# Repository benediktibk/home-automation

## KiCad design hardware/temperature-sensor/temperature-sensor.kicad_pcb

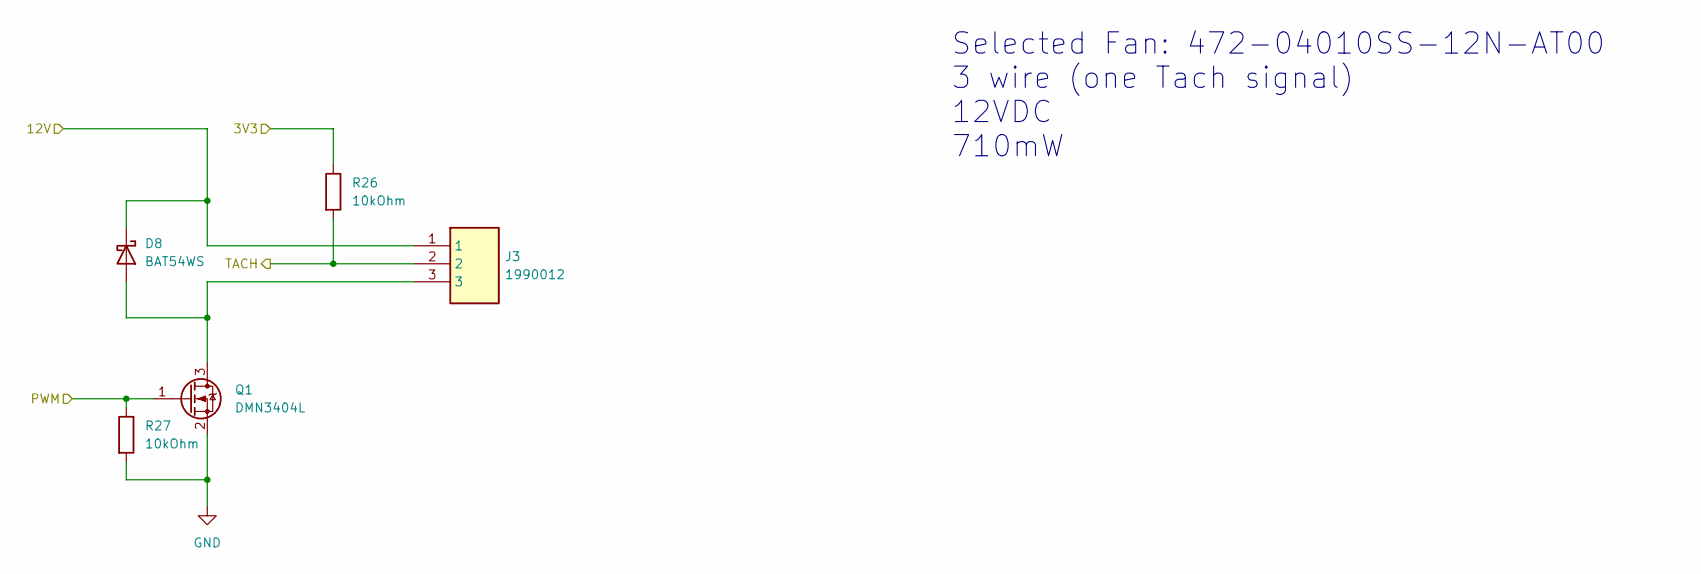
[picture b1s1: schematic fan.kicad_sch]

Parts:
D8: BAT54WS; D_SOD-323; Mouser Part Number 637-BAT54WS
J3: 1990012; Mouser Part Number 651-1990012
Q1: DMN3404L; SOT-23; Mouser Part Number 621-DMN3404L-7
R26, R27: 10kOhm; R_0603_1608Metric_Pad0.98x0.95mm_HandSolder; Mouser Part Number 652-CR0603FX-1002ELF

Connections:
/3V3: R26.1; also elsewhere on the board
/12V: D8.1 (K), J3.1; also elsewhere on the board
/Fan/PWM: Q1.1 (G), R27.1; also elsewhere on the board
/Fan/TACH: J3.2, R26.2; also elsewhere on the board
GND: Q1.2 (S), R27.2; also elsewhere on the board
unnamed: D8.2 (A), J3.3, Q1.3 (D)

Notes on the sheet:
Selected Fan: 472-04010SS-12N-AT00 3 wire (one Tach signal) 12VDC 710mW

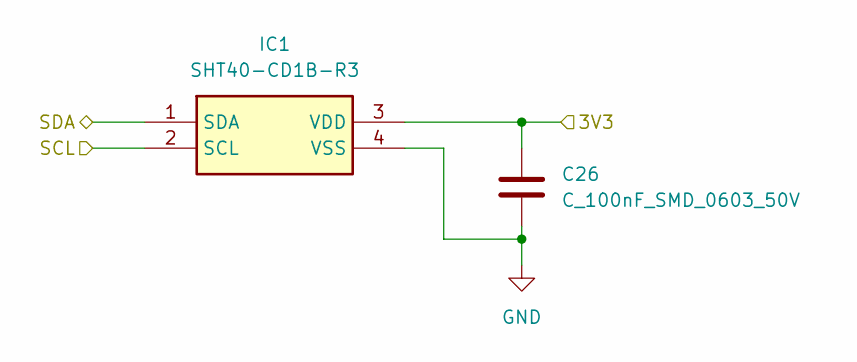
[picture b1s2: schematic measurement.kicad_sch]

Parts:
C26: C_100nF_SMD_0603_50V; C_0603_1608Metric_Pad1.08x0.95mm_HandSolder; Mouser Part Number 581-KGM15BR71H104KM
IC1: SHT40-CD1B-R3; SHT40CD1BR3; Mouser Part Number 403-SHT40-CD1B-R3

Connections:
/3V3: C26.1, IC1.3 (VDD); also elsewhere on the board
/MCU/SCL: IC1.2 (SCL); also elsewhere on the board
/MCU/SDA: IC1.1 (SDA); also elsewhere on the board
GND: C26.2, IC1.4 (VSS); also elsewhere on the board

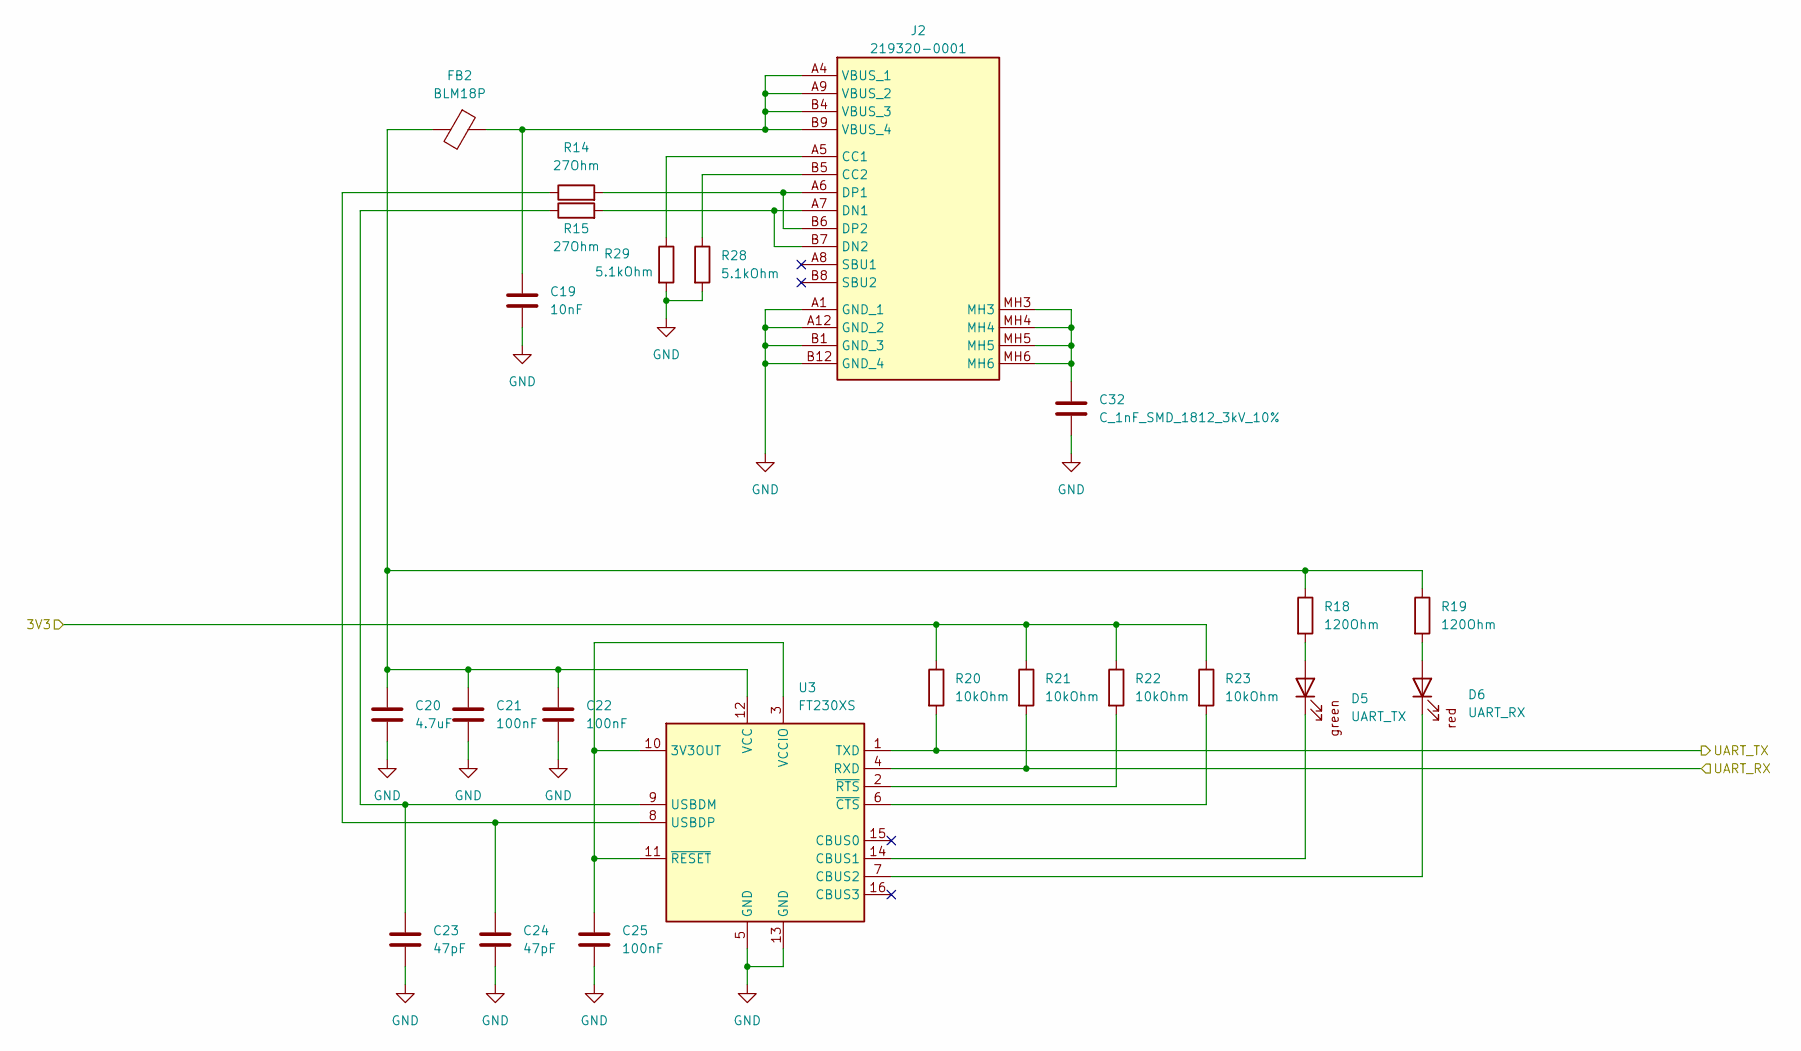
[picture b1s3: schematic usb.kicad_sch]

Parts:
C19: 10nF; C_0603_1608Metric_Pad1.08x0.95mm_HandSolder; Mouser Part Number 80-C0603C103M5R3121
C20: 4.7uF; C_0805_2012Metric_Pad1.18x1.45mm_HandSolder; Mouser Part Number 187-CL21A475KBQNNNE
C21, C22, C25: 100nF; C_0603_1608Metric_Pad1.08x0.95mm_HandSolder; Mouser Part Number 581-KGM15BR71H104KM
C23, C24: 47pF; C_0603_1608Metric_Pad1.08x0.95mm_HandSolder; Mouser Part Number 791-0603N470J101CT
C32: C_1nF_SMD_1812_3kV_10%; C_0603_1608Metric_Pad1.08x0.95mm_HandSolder; Mouser Part Number 791-1812B102K302CT
D5: UART_TX; D_0603_1608Metric_Pad1.05x0.95mm_HandSolder; Mouser Part Number 604-AP1608SGC
D6: UART_RX; D_0603_1608Metric_Pad1.05x0.95mm_HandSolder; Mouser Part Number 859-LTST-C190KDKT10A
FB2: BLM18P; R_0603_1608Metric_Pad0.98x0.95mm_HandSolder; Mouser Part Number 81-BLM11P300S
J2: 219320-0001; 2193200001; Mouser Part Number 538-219320-0001
R14, R15: 27Ohm; R_0603_1608Metric_Pad0.98x0.95mm_HandSolder; Mouser Part Number 603-RC0603FR-0727RL
R18, R19: 120Ohm; R_0603_1608Metric_Pad0.98x0.95mm_HandSolder; Mouser Part Number 603-RC0603FR-07120RL
R20, R21, R22, R23: 10kOhm; R_0603_1608Metric_Pad0.98x0.95mm_HandSolder; Mouser Part Number 652-CR0603FX-1002ELF
R28, R29: 5.1kOhm; R_0603_1608Metric_Pad0.98x0.95mm_HandSolder; Mouser Part Number 303-0603SAF5101T5E
U3: FT230XS; SSOP-16_3.9x4.9mm_P0.635mm; Mouser Part Number 895-FT230XS-R

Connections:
/3V3: R20.1, R21.1, R22.1, R23.1; also elsewhere on the board
/MCU/UART_RX: R20.2, U3.1 (TXD); also elsewhere on the board
/MCU/UART_TX: R21.2, U3.4 (RXD); also elsewhere on the board
GND: C19.2, C20.2, C21.2, C22.2, C23.2, C24.2, C25.2, C32.2, J2.A1 (GND_1), J2.A12 (GND_2), J2.B1 (GND_3), J2.B12 (GND_4), R28.2, R29.2, U3.5 (GND), U3.13 (GND); also elsewhere on the board
unnamed: C32.1, J2.MH3, J2.MH4, J2.MH5, J2.MH6
unnamed: D5.2 (A), R18.2
unnamed: D5.1 (K), U3.14 (CBUS1)
unnamed: D6.2 (A), R19.2
unnamed: D6.1 (K), U3.7 (CBUS2)
unnamed: J2.A5 (CC1), R29.1
unnamed: J2.B5 (CC2), R28.1
unnamed: J2.A7 (DN1), J2.B7 (DN2), R15.2
unnamed: J2.A6 (DP1), J2.B6 (DP2), R14.2
unnamed: C19.1, FB2.1, J2.A4 (VBUS_1), J2.A9 (VBUS_2), J2.B4 (VBUS_3), J2.B9 (VBUS_4)
unnamed: C25.1, U3.3 (VCCIO), U3.10 (3V3OUT), U3.11 (~RESET)
unnamed: C23.1, R15.1, U3.9 (USBDM)
unnamed: C24.1, R14.1, U3.8 (USBDP)
unnamed: C20.1, C21.1, C22.1, FB2.2, R18.1, R19.1, U3.12 (VCC)
unnamed: R23.2, U3.6 (~CTS)
unnamed: R22.2, U3.2 (~RTS)

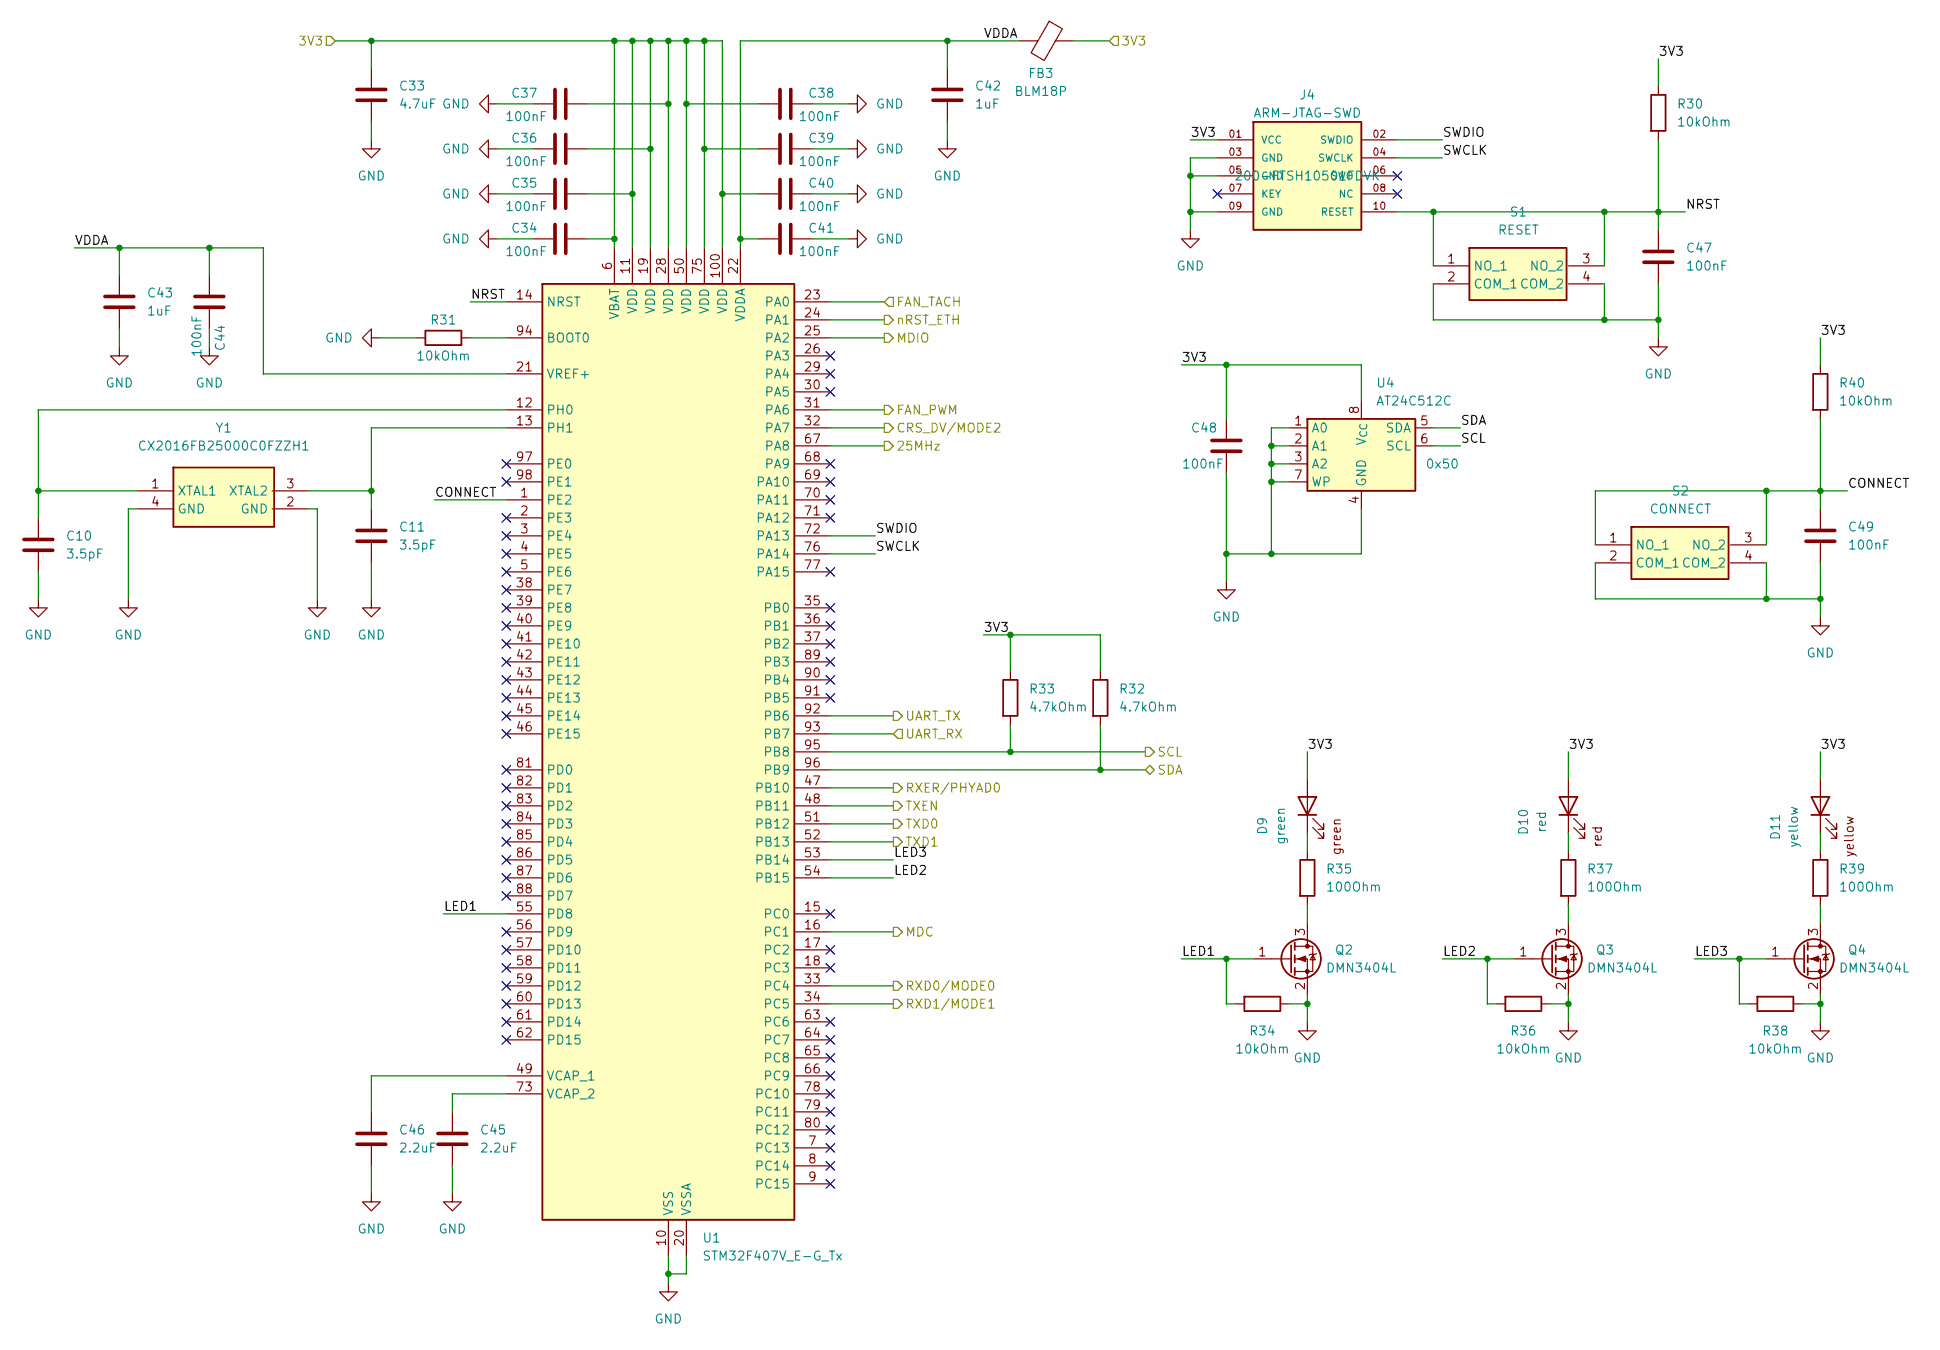
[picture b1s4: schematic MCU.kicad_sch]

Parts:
C10, C11: 3.5pF; C_0603_1608Metric_Pad1.08x0.95mm_HandSolder; Mouser Part Number 80-CBR06C359B5GAC
C33: 4.7uF; C_0805_2012Metric_Pad1.18x1.45mm_HandSolder; Mouser Part Number 187-CL21A475KBQNNNE
C34, C35, C36, C37, C38, C39, C40, C41, C44, C47, C48, C49: 100nF; C_0603_1608Metric_Pad1.08x0.95mm_HandSolder; Mouser Part Number 581-KGM15BR71H104KM
C42, C43: 1uF; C_0603_1608Metric_Pad1.08x0.95mm_HandSolder; Mouser Part Number 963-UMK107BJ105KA-T
C45, C46: 2.2uF; C_0603_1608Metric_Pad1.08x0.95mm_HandSolder; Mouser Part Number 187-CL10A225KP8NNND
D9: green; D_0603_1608Metric_Pad1.05x0.95mm_HandSolder; Mouser Part Number 604-AP1608SGC
D10: red; D_0603_1608Metric_Pad1.05x0.95mm_HandSolder; Mouser Part Number 859-LTST-C190KDKT10A
D11: yellow; D_0603_1608Metric_Pad1.05x0.95mm_HandSolder; Mouser Part Number 604-APG1608SYKC/T
FB3: BLM18P; R_0603_1608Metric_Pad0.98x0.95mm_HandSolder; Mouser Part Number 81-BLM11P300S
J4: ARM-JTAG-SWD; SAMTEC_FTSH-105-01-F-DV-P-TR; Mouser Part Number 200-FTSH10501FDVK
Q2, Q3, Q4: DMN3404L; SOT-23; Mouser Part Number 621-DMN3404L-7
R30, R31, R34, R36, R38, R40: 10kOhm; R_0603_1608Metric_Pad0.98x0.95mm_HandSolder; Mouser Part Number 652-CR0603FX-1002ELF
R32, R33: 4.7kOhm; R_0603_1608Metric_Pad0.98x0.95mm_HandSolder; Mouser Part Number 652-CR0603FX-4701ELF
R35, R37, R39: 100Ohm; R_0603_1608Metric_Pad0.98x0.95mm_HandSolder; Mouser Part Number 279-CRGH0603F100R
S1: RESET; TS046673BK100SMT; Mouser Part Number 179-TS046673BK100SMT
S2: CONNECT; TS046673BK100SMT; Mouser Part Number 179-TS046673BK100SMT
U1: STM32F407V_E-G_Tx; LQFP-100_14x14mm_P0.5mm; Mouser Part Number 511-STM32F407VGT6
U4: AT24C512C; SOIC127P600X175-8N; Mouser Part Number 556-AT24C512C-SSHM-T
Y1: CX2016FB25000C0FZZH1; Mouser Part Number 581-CX2016FB25C0FZZH

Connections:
/3V3: C33.1, C34.1, C35.1, C36.1, C37.1, C38.1, C39.1, C40.1, C48.1, D9.2 (A), D10.2 (A), D11.2 (A), FB3.1, J4.01 (VCC), R30.1, R32.1, R33.1, R40.1, U1.6 (VBAT), U1.11 (VDD), U1.19 (VDD), U1.28 (VDD), U1.50 (VDD), U1.75 (VDD), U1.100 (VDD), U4.8 (V_{CC}); also elsewhere on the board
/Ethernet/25MHz: U1.67 (PA8); also elsewhere on the board
/Ethernet/CRS_DV/MODE2: U1.32 (PA7); also elsewhere on the board
/Ethernet/MDC: U1.16 (PC1); also elsewhere on the board
/Ethernet/MDIO: U1.25 (PA2); also elsewhere on the board
/Ethernet/RXD0/MODE0: U1.33 (PC4); also elsewhere on the board
/Ethernet/RXD1/MODE1: U1.34 (PC5); also elsewhere on the board
/Ethernet/RXER/PHYAD0: U1.47 (PB10); also elsewhere on the board
/Ethernet/TXD0: U1.51 (PB12); also elsewhere on the board
/Ethernet/TXD1: U1.52 (PB13); also elsewhere on the board
/Ethernet/TXEN: U1.48 (PB11); also elsewhere on the board
/Ethernet/nRST: U1.24 (PA1); also elsewhere on the board
/Fan/PWM: U1.31 (PA6); also elsewhere on the board
/Fan/TACH: U1.23 (PA0); also elsewhere on the board
/MCU/CONNECT: C49.1, R40.2, S2.1 (NO_1), S2.3 (NO_2), U1.1 (PE2)
/MCU/LED1: Q2.1 (G), R34.2, U1.55 (PD8)
/MCU/LED2: Q3.1 (G), R36.2, U1.54 (PB15)
/MCU/LED3: Q4.1 (G), R38.2, U1.53 (PB14)
/MCU/NRST: C47.1, J4.10 (RESET), R30.2, S1.1 (NO_1), S1.3 (NO_2), U1.14 (NRST)
/MCU/SCL: R33.2, U1.95 (PB8), U4.6 (SCL); also elsewhere on the board
/MCU/SDA: R32.2, U1.96 (PB9), U4.5 (SDA); also elsewhere on the board
/MCU/SWCLK: J4.04 (SWCLK), U1.76 (PA14)
/MCU/SWDIO: J4.02 (SWDIO), U1.72 (PA13)
/MCU/UART_RX: U1.93 (PB7); also elsewhere on the board
/MCU/UART_TX: U1.92 (PB6); also elsewhere on the board
/MCU/VDDA: C41.1, C42.1, C43.1, C44.1, FB3.2, U1.21 (VREF+), U1.22 (VDDA)
GND: C10.2, C11.2, C33.2, C34.2, C35.2, C36.2, C37.2, C38.2, C39.2, C40.2, C41.2, C42.2, C43.2, C44.2, C45.2, C46.2, C47.2, C48.2, C49.2, J4.03 (GND), J4.05 (GND), J4.09 (GND), Q2.2 (S), Q3.2 (S), Q4.2 (S), R31.1, R34.1, R36.1, R38.1, S1.2 (COM_1), S1.4 (COM_2), S2.2 (COM_1), S2.4 (COM_2), U1.10 (VSS), U1.20 (VSSA), U1.27 (VSS), U1.74 (VSS), U1.99 (VSS), U4.1 (A0), U4.2 (A1), U4.3 (A2), U4.4 (GND), U4.7 (WP), Y1.2 (GND), Y1.4 (GND); also elsewhere on the board
unnamed: D9.1 (K), R35.1
unnamed: D10.1 (K), R37.1
unnamed: D11.1 (K), R39.1
unnamed: Q2.3 (D), R35.2
unnamed: Q3.3 (D), R37.2
unnamed: Q4.3 (D), R39.2
unnamed: R31.2, U1.94 (BOOT0)
unnamed: C10.1, U1.12 (PH0), Y1.1 (XTAL1)
unnamed: C11.1, U1.13 (PH1), Y1.3 (XTAL2)
unnamed: C46.1, U1.49 (VCAP_1)
unnamed: C45.1, U1.73 (VCAP_2)

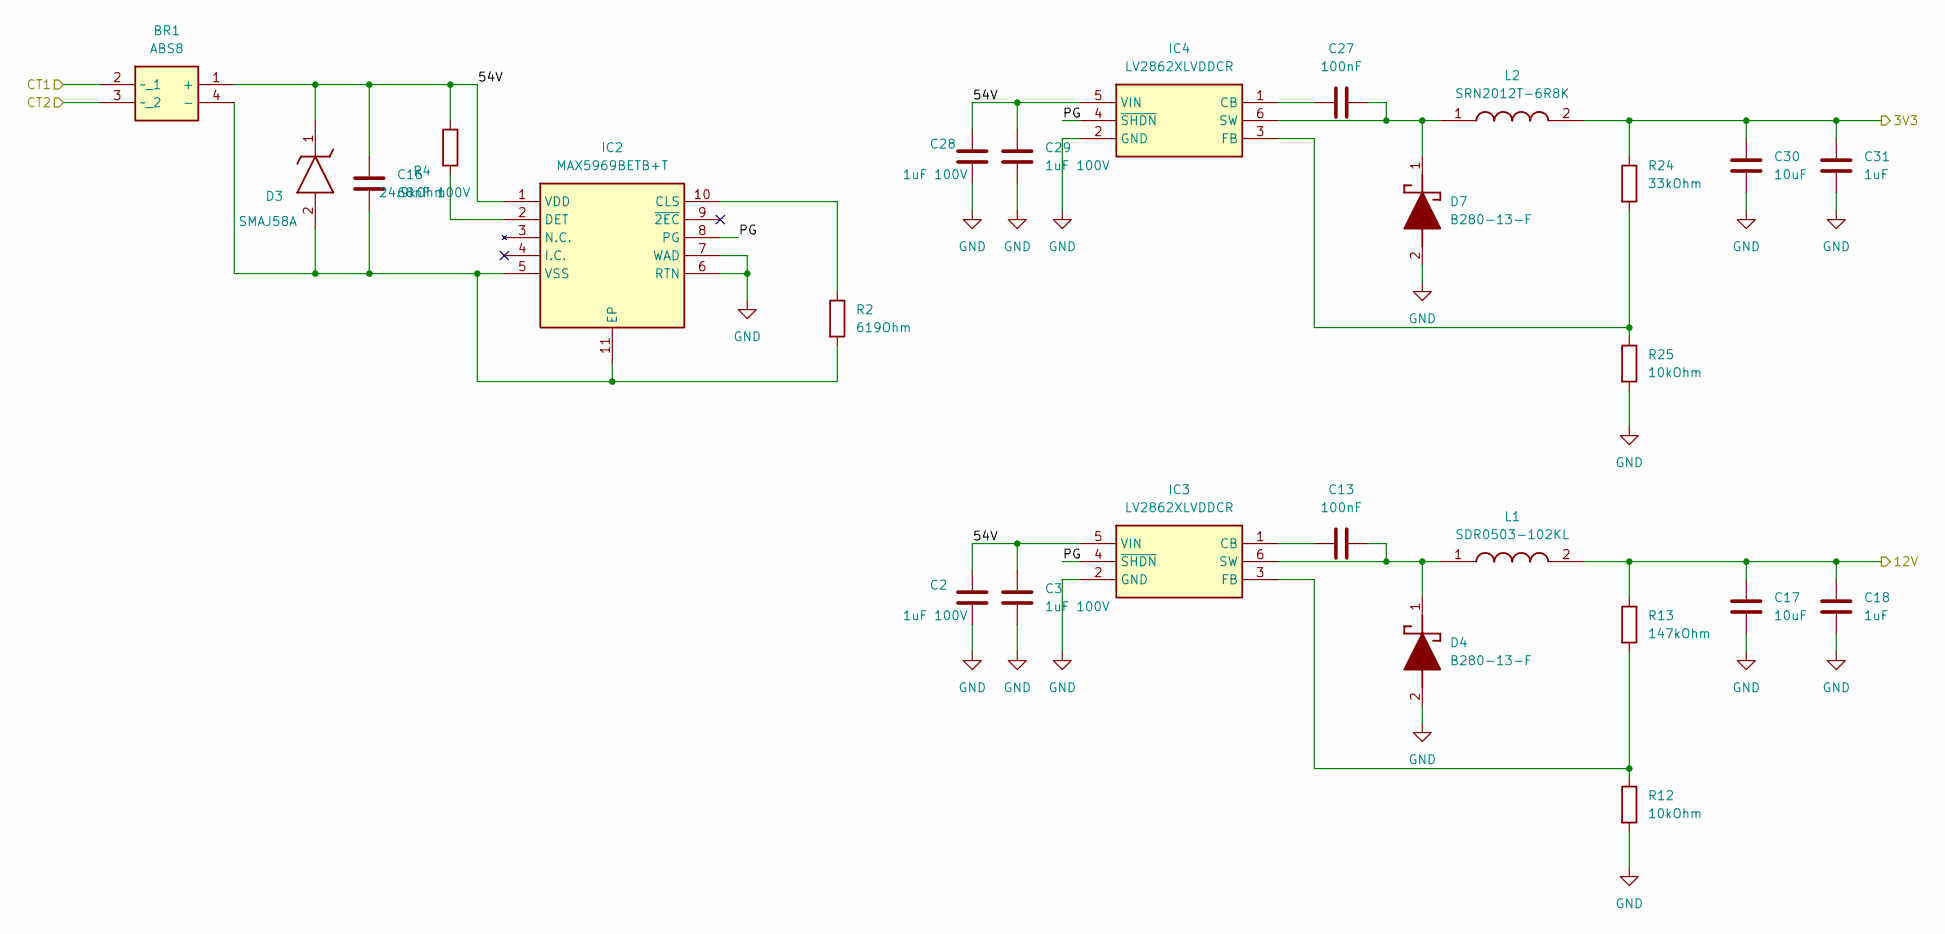
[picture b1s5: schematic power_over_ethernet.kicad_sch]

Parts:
BR1: ABS8; Mouser Part Number 637-ABS8
C2, C3, C28, C29: 1uF 100V; C_0603_1608Metric_Pad1.08x0.95mm_HandSolder; Mouser Part Number 810-C1608X7R2A105K08
C13, C27: 100nF; C_0603_1608Metric_Pad1.08x0.95mm_HandSolder; Mouser Part Number 581-KGM15BR71H104KM
C16: 68nF 100V; C_0603_1608Metric_Pad1.08x0.95mm_HandSolder; Mouser Part Number 791-0603B683K101CT
C17, C30: 10uF; C_1210_3225Metric_Pad1.33x2.70mm_HandSolder; Mouser Part Number 187-CL31A106MBHNNNE
C18, C31: 1uF; C_0603_1608Metric_Pad1.08x0.95mm_HandSolder; Mouser Part Number 963-UMK107BJ105KA-T
D3: SMAJ58A; DIOM5026X229N; Mouser Part Number 576-SMAJ58A
D4, D7: B280-13-F; DIOM5336X250N; Mouser Part Number 621-B280-13-F
IC2: MAX5969BETB+T; SON50P300X300X80-11N; Mouser Part Number 700-MAX5969BETB+T
IC3, IC4: LV2862XLVDDCR; SOT95P280X110-6N; Mouser Part Number 595-LV2862XLVDDCR
L1: SDR0503-102KL; SDR0503102KL; Mouser Part Number 652-SDR0503-102KL
L2: SRN2012T-6R8K; INDPM2012X120N; Mouser Part Number 652-SRN2012T-6R8K
R2: 619Ohm; R_0603_1608Metric_Pad0.98x0.95mm_HandSolder; Mouser Part Number 603-RT0603FRE07619RL
R4: 24.9kOhm; R_0603_1608Metric_Pad0.98x0.95mm_HandSolder; Mouser Part Number 594-MCT06030C2492FP5
R12, R25: 10kOhm; R_0603_1608Metric_Pad0.98x0.95mm_HandSolder; Mouser Part Number 652-CR0603FX-1002ELF
R13: 147kOhm; R_0603_1608Metric_Pad0.98x0.95mm_HandSolder; Mouser Part Number 594-MCT06030C1473FP5
R24: 33kOhm; R_0603_1608Metric_Pad0.98x0.95mm_HandSolder; Mouser Part Number 594-MCT06030C3302FP5

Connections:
/3V3: C30.1, C31.1, L2.2, R24.1; also elsewhere on the board
/12V: C17.1, C18.1, L1.2, R13.1; also elsewhere on the board
/Ethernet/CT1: BR1.2 (~_1); also elsewhere on the board
/Ethernet/CT2: BR1.3 (~_2); also elsewhere on the board
/Power over Ethernet/54V: BR1.1 (+), C2.1, C3.1, C16.1, C28.1, C29.1, D3.1 (K), IC2.1 (VDD), IC3.5 (VIN), IC4.5 (VIN), R4.1
/Power over Ethernet/PG: IC2.8 (PG), IC3.4 (~SHDN), IC4.4 (~SHDN)
GND: C2.2, C3.2, C17.2, C18.2, C28.2, C29.2, C30.2, C31.2, D4.2 (A), D7.2 (A), IC2.6 (RTN), IC2.7 (WAD), IC3.2 (GND), IC4.2 (GND), R12.2, R25.2; also elsewhere on the board
unnamed: BR1.4 (-), C16.2, D3.2 (A), IC2.5 (VSS), IC2.11 (EP), R2.2
unnamed: C13.1, D4.1 (K), IC3.6 (SW), L1.1
unnamed: C27.1, D7.1 (K), IC4.6 (SW), L2.1
unnamed: IC2.10 (CLS), R2.1
unnamed: IC2.2 (DET), R4.2
unnamed: C13.2, IC3.1 (CB)
unnamed: IC3.3 (FB), R12.1, R13.2
unnamed: C27.2, IC4.1 (CB)
unnamed: IC4.3 (FB), R24.2, R25.1

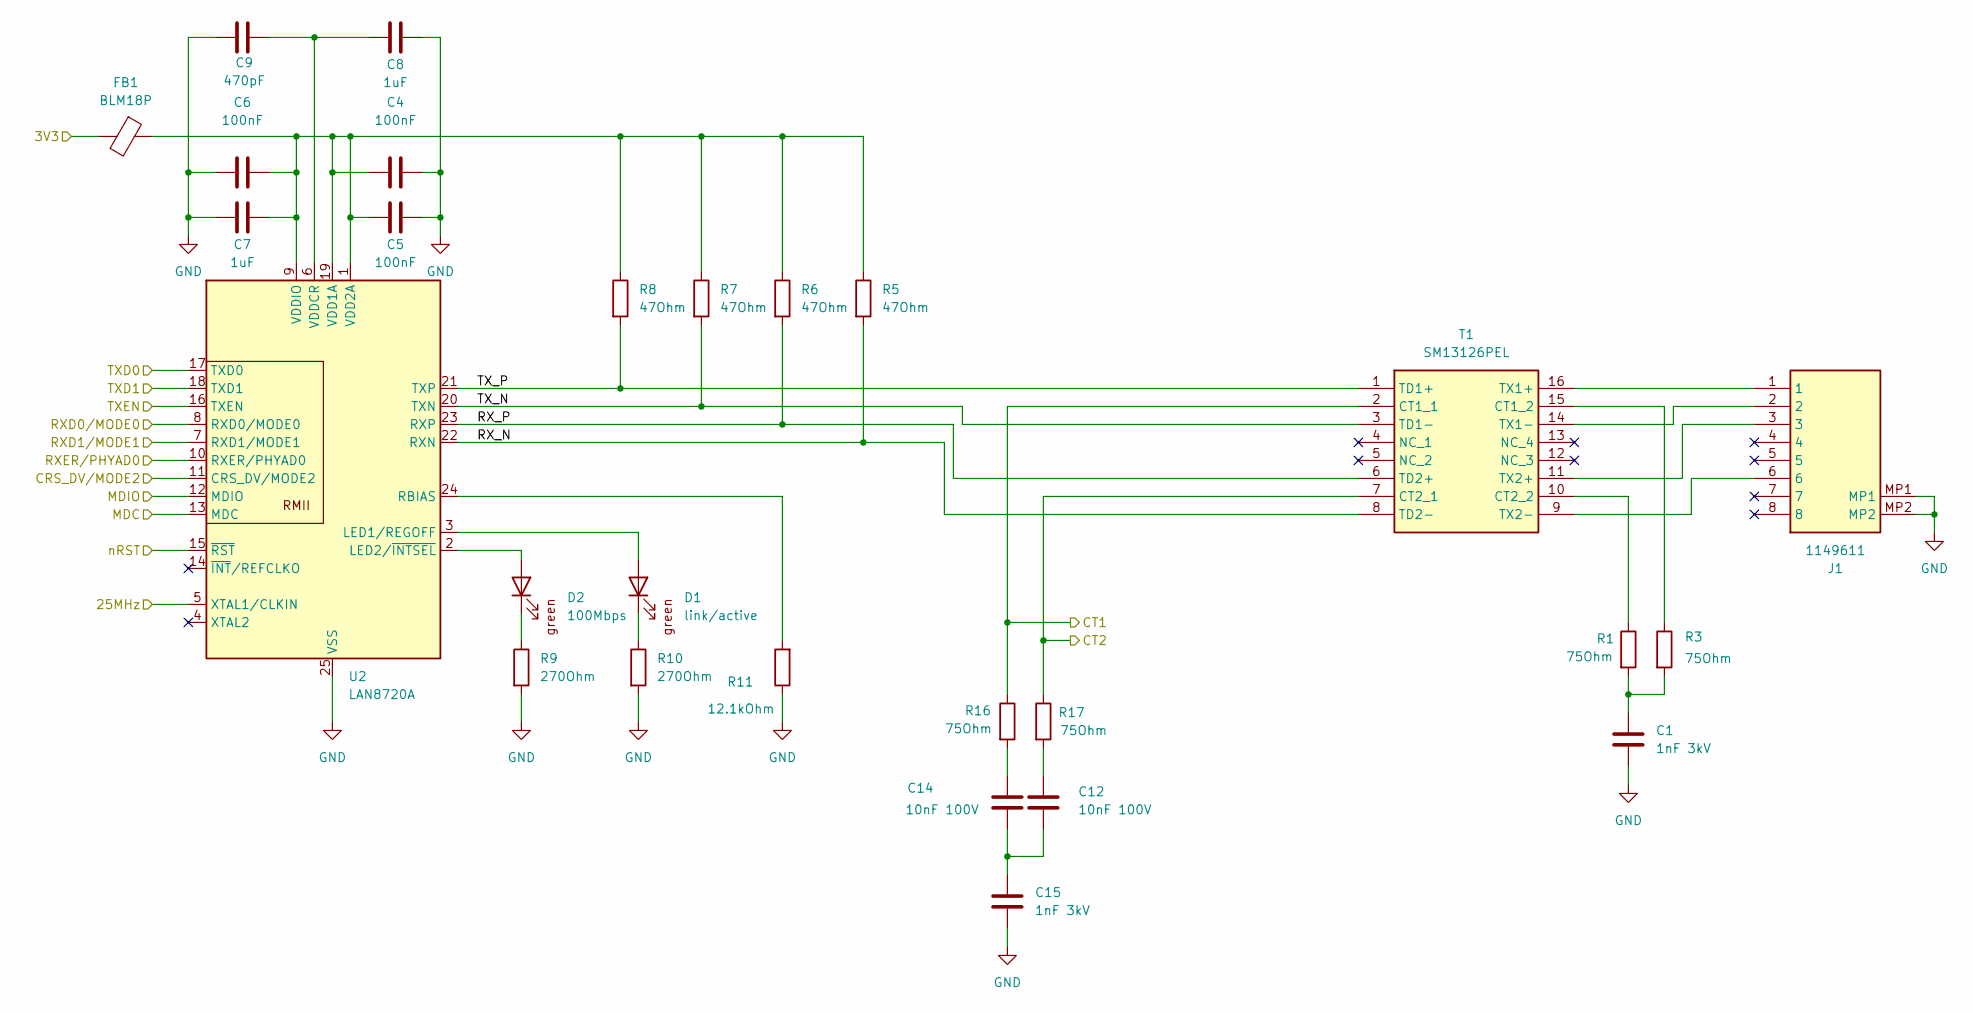
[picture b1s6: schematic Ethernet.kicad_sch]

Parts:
C1, C15: 1nF 3kV; C_0603_1608Metric_Pad1.08x0.95mm_HandSolder; Mouser Part Number 791-1812B102K302CT
C4, C5, C6: 100nF; C_0603_1608Metric_Pad1.08x0.95mm_HandSolder; Mouser Part Number 581-KGM15BR71H104KM
C7, C8: 1uF; C_0603_1608Metric_Pad1.08x0.95mm_HandSolder; Mouser Part Number 963-UMK107BJ105KA-T
C9: 470pF; C_0603_1608Metric_Pad1.08x0.95mm_HandSolder; Mouser Part Number 187-CL10C471JB81PNC
C12, C14: 10nF 100V; C_0603_1608Metric_Pad1.08x0.95mm_HandSolder; Mouser Part Number 581-06031C103K4T2A
D1: link/active; D_0603_1608Metric_Pad1.05x0.95mm_HandSolder; Mouser Part Number 604-AP1608SGC
D2: 100Mbps; D_0603_1608Metric_Pad1.05x0.95mm_HandSolder; Mouser Part Number 604-AP1608SGC
FB1: BLM18P; R_0603_1608Metric_Pad0.98x0.95mm_HandSolder; Mouser Part Number 81-BLM11P300S
J1: 1149611; Mouser Part Number 651-1149611
R1, R3, R16, R17: 75Ohm; R_0603_1608Metric_Pad0.98x0.95mm_HandSolder; Mouser Part Number 71-CRCW060375R0FKEAC
R5, R6, R7, R8: 47Ohm; R_0603_1608Metric_Pad0.98x0.95mm_HandSolder; Mouser Part Number 603-AC0603FR-1347RL
R9, R10: 270Ohm; R_0603_1608Metric_Pad0.98x0.95mm_HandSolder; Mouser Part Number 603-RE0603FRE07270RL
R11: 12.1kOhm; R_0603_1608Metric_Pad0.98x0.95mm_HandSolder; Mouser Part Number 603-RT0603FRE1012K1L
T1: SM13126PEL; Mouser Part Number 652-SM13126PEL
U2: LAN8720A; LAN8720A-CP-ABC; Mouser Part No 579-LAN8720ACPABC

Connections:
/3V3: FB1.2; also elsewhere on the board
/Ethernet/25MHz: U2.5 (XTAL1/CLKIN); also elsewhere on the board
/Ethernet/CRS_DV/MODE2: U2.11 (CRS_DV/MODE2); also elsewhere on the board
/Ethernet/CT1: R16.1, T1.2 (CT1_1); also elsewhere on the board
/Ethernet/CT2: R17.1, T1.7 (CT2_1); also elsewhere on the board
/Ethernet/MDC: U2.13 (MDC); also elsewhere on the board
/Ethernet/MDIO: U2.12 (MDIO); also elsewhere on the board
/Ethernet/RXD0/MODE0: U2.8 (RXD0/MODE0); also elsewhere on the board
/Ethernet/RXD1/MODE1: U2.7 (RXD1/MODE1); also elsewhere on the board
/Ethernet/RXER/PHYAD0: U2.10 (RXER/PHYAD0); also elsewhere on the board
/Ethernet/RX_N: R5.2, T1.8 (TD2-), U2.22 (RXN)
/Ethernet/RX_P: R6.2, T1.6 (TD2+), U2.23 (RXP)
/Ethernet/TXD0: U2.17 (TXD0); also elsewhere on the board
/Ethernet/TXD1: U2.18 (TXD1); also elsewhere on the board
/Ethernet/TXEN: U2.16 (TXEN); also elsewhere on the board
/Ethernet/TX_N: R7.2, T1.3 (TD1-), U2.20 (TXN)
/Ethernet/TX_P: R8.2, T1.1 (TD1+), U2.21 (TXP)
/Ethernet/nRST: U2.15 (~RST); also elsewhere on the board
GND: C1.2, C4.1, C5.2, C6.2, C7.2, C8.1, C9.2, C15.2, J1.MP1, J1.MP2, R9.2, R10.2, R11.1, U2.25 (VSS); also elsewhere on the board
unnamed: C1.1, R1.2, R3.2
unnamed: C12.1, R17.2
unnamed: C12.2, C14.2, C15.1
unnamed: C14.1, R16.2
unnamed: D1.2 (A), U2.3 (LED1/REGOFF)
unnamed: D1.1 (K), R10.1
unnamed: D2.2 (A), U2.2 (LED2/~INTSEL)
unnamed: D2.1 (K), R9.1
unnamed: R3.1, T1.15 (CT1_2)
unnamed: R1.1, T1.10 (CT2_2)
unnamed: J1.1, T1.16 (TX1+)
unnamed: J1.2, T1.14 (TX1-)
unnamed: J1.3, T1.11 (TX2+)
unnamed: J1.6, T1.9 (TX2-)
unnamed: R11.2, U2.24 (RBIAS)
unnamed: C4.2, C5.1, C6.1, C7.1, FB1.1, R5.1, R6.1, R7.1, R8.1, U2.1 (VDD2A), U2.9 (VDDIO), U2.19 (VDD1A)
unnamed: C8.2, C9.1, U2.6 (VDDCR)

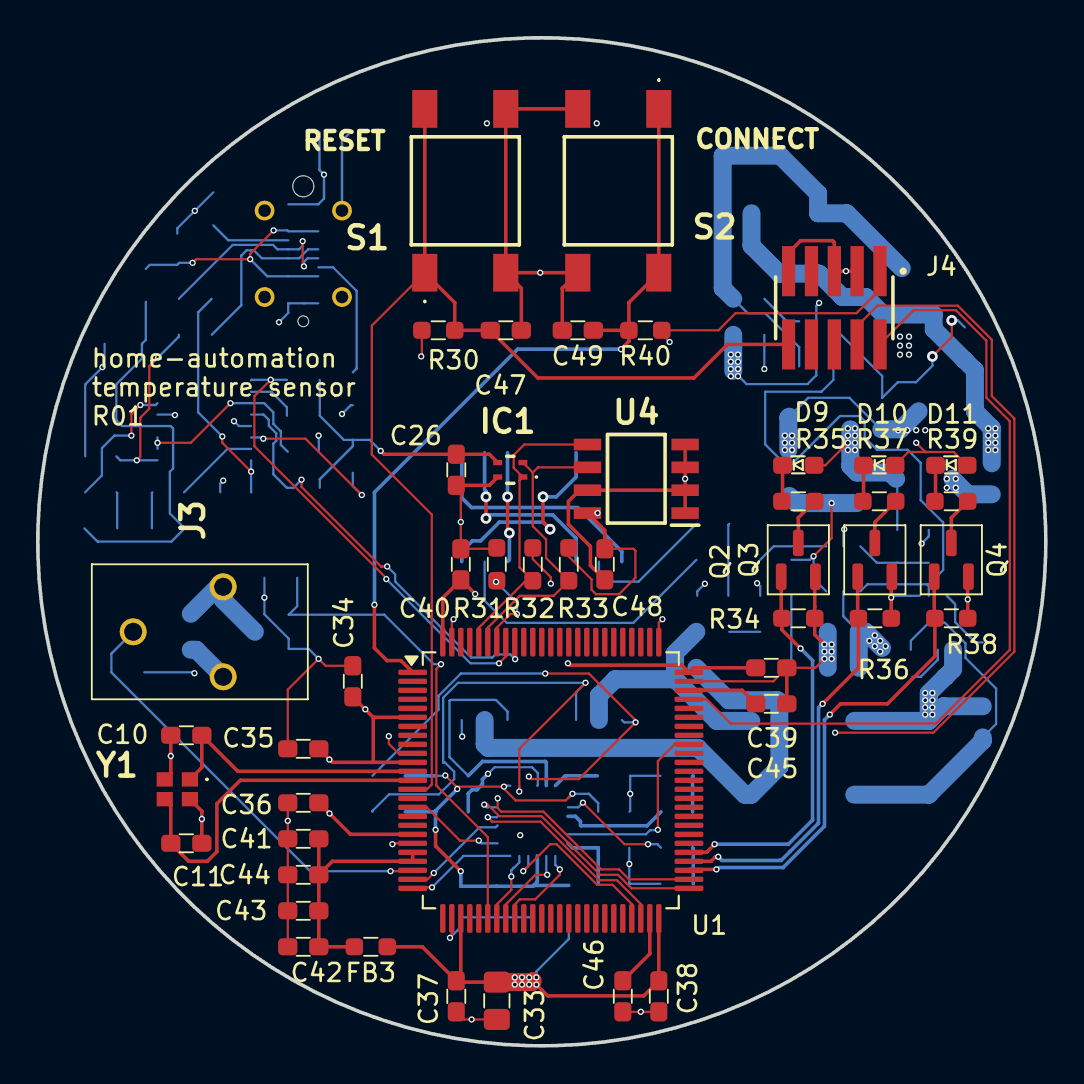
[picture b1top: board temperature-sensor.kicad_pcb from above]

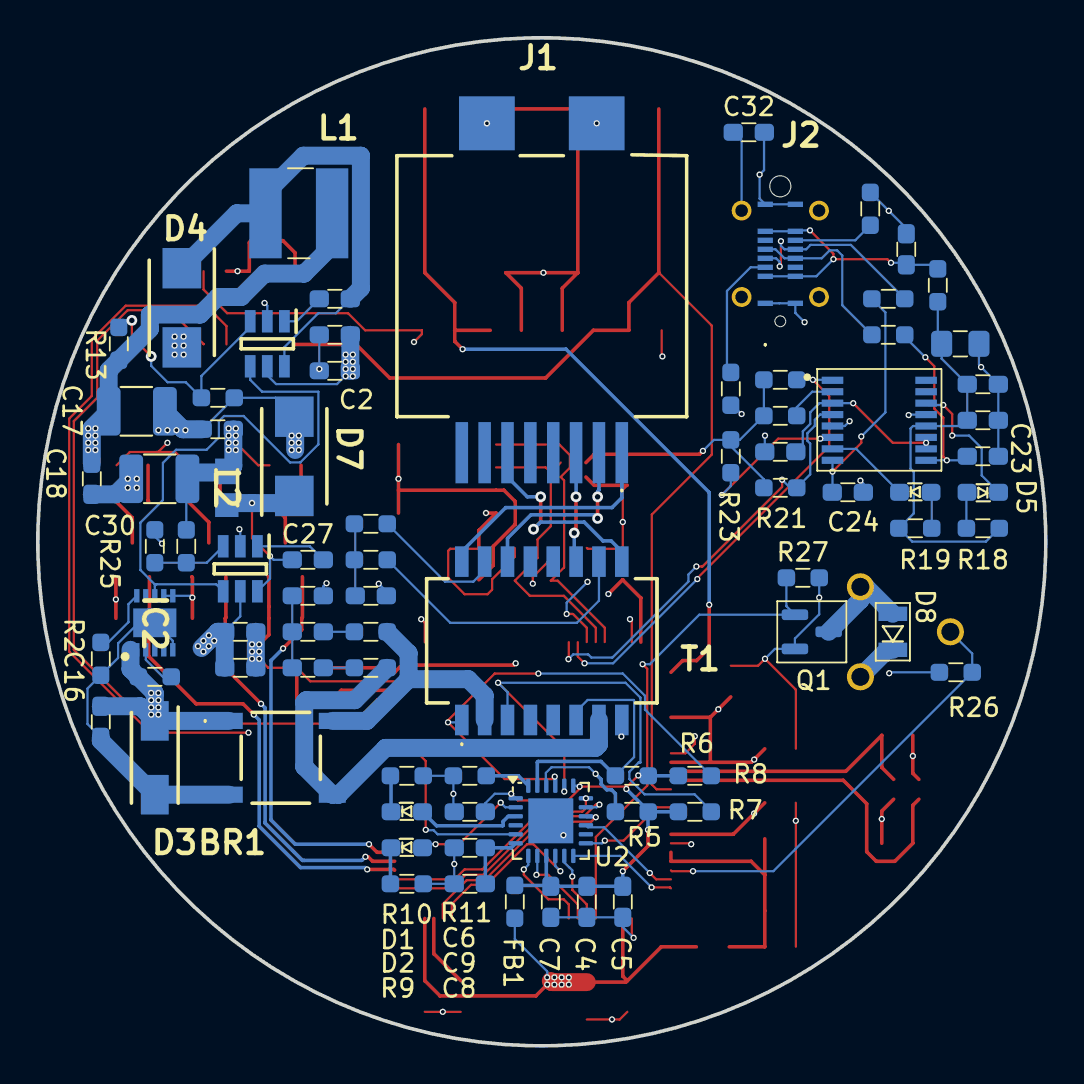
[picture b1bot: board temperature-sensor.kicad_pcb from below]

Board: 4 copper layers, 56.0 x 56.0 mm, 126 parts (80 on the bottom side), 90 nets.

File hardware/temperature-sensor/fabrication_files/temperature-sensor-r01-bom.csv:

"Reference","Value","Qty","Mouser Part Number","RS order number"
"BR1","ABS8","1","637-ABS8",""
"C1,C15","1nF 3kV","2","791-1812B102K302CT",""
"C2,C3,C28,C29","1uF 100V","4","810-C1608X7R2A105K08",""
"C4,C5,C6,C13,C21,C22,C25,C27,C34,C35,C36,C37,C38,C39,C40,C41,C44,C47,C48,C49","100nF","20","581-KGM15BR71H104KM","242-7372"
"C7,C8,C18,C31,C42,C43","1uF","6","963-UMK107BJ105KA-T","103-4112"
"C9","470pF","1","187-CL10C471JB81PNC",""
"C10,C11","3.5pF","2","80-CBR06C359B5GAC","103-4112"
"C12,C14","10nF 100V","2","581-06031C103K4T2A","135-6315"
"C16","68nF 100V","1","791-0603B683K101CT",""
"C17,C30","10uF","2","187-CL31A106MBHNNNE","172-1575"
"C19","10nF","1","80-C0603C103M5R3121","135-6315"
"C20,C33","4.7uF","2","187-CL21A475KBQNNNE","113-8707"
"C23,C24","47pF","2","791-0603N470J101CT","135-6508"
"C26","C_100nF_SMD_0603_50V","1","581-KGM15BR71H104KM","242-7372"
"C32","C_1nF_SMD_1812_3kV_10%","1","791-1812B102K302CT",""
"C45,C46","2.2uF","2","187-CL10A225KP8NNND","103-4112"
"D1","link/active","1","604-AP1608SGC","466-3706"
"D2","100Mbps","1","604-AP1608SGC","466-3706"
"D3","SMAJ58A","1","576-SMAJ58A",""
"D4,D7","B280-13-F","2","621-B280-13-F",""
"D5","UART_TX","1","604-AP1608SGC","466-3706"
"D6","UART_RX","1","859-LTST-C190KDKT10A","861-0090"
"D8","BAT54WS","1","637-BAT54WS","738-4844"
"D9","green","1","604-AP1608SGC","466-3706"
"D10","red","1","859-LTST-C190KDKT10A","861-0090"
"D11","yellow","1","604-APG1608SYKC/T","861-0087"
"FB1,FB2,FB3","BLM18P","3","81-BLM11P300S","724-1403"
"IC1","SHT40-CD1B-R3","1","403-SHT40-CD1B-R3",""
"IC2","MAX5969BETB+T","1","700-MAX5969BETB+T",""
"IC3,IC4","LV2862XLVDDCR","2","595-LV2862XLVDDCR",""
"J1","1149611","1","651-1149611",""
"J2","219320-0001","1","538-219320-0001",""
"J3","1990012","1","651-1990012",""
"J4","ARM-JTAG-SWD","1","200-FTSH10501FDVK","159-2372"
"L1","SDR0503-102KL","1","652-SDR0503-102KL",""
"L2","SRN2012T-6R8K","1","652-SRN2012T-6R8K",""
"Q1,Q2,Q3,Q4","DMN3404L","4","621-DMN3404L-7","751-4171"
"R1,R3,R16,R17","75Ohm","4","71-CRCW060375R0FKEAC ",""
"R2","619Ohm","1","603-RT0603FRE07619RL","125-1173"
"R4","24.9kOhm","1","594-MCT06030C2492FP5",""
"R5,R6,R7,R8","47Ohm","4","603-AC0603FR-1347RL","901-3513"
"R9,R10","270Ohm","2","603-RE0603FRE07270RL",""
"R11","12.1kOhm","1","603-RT0603FRE1012K1L",""
"R12,R20,R21,R22,R23,R25,R26,R27,R30,R31,R34,R36,R38,R40","10kOhm","14","652-CR0603FX-1002ELF","125-1173"
"R13","147kOhm","1","594-MCT06030C1473FP5",""
"R14,R15","27Ohm","2","603-RC0603FR-0727RL","213-2058"
"R18,R19","120Ohm","2","603-RC0603FR-07120RL","199-5452"
"R24","33kOhm","1","594-MCT06030C3302FP5",""
"R28,R29","5.1kOhm","2","303-0603SAF5101T5E",""
"R32,R33","4.7kOhm","2","652-CR0603FX-4701ELF","901-3581"
"R35,R37,R39","100Ohm","3","279-CRGH0603F100R","125-1172"
"S1","RESET","1","179-TS046673BK100SMT",""
"S2","CONNECT","1","179-TS046673BK100SMT",""
"T1","SM13126PEL","1","652-SM13126PEL",""
"U1","STM32F407V_E-G_Tx","1","511-STM32F407VGT6",""
"U2","LAN8720A","1","579-LAN8720ACPABC",""
"U3","FT230XS","1","895-FT230XS-R","757-0010"
"U4","AT24C512C","1","556-AT24C512C-SSHM-T","197-5331"
"Y1","CX2016FB25000C0FZZH1","1","581-CX2016FB25C0FZZH",""

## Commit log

2024-12-29 add empty KiCAD project for temperature sensor
2024-12-29 add basic required parts
2025-03-16 add components for temperature sensor
2025-07-07 extend schematic of ethernet
2025-07-08 add quartz
2025-07-09 replace ethernet transformer
2025-07-09 update PCB from schematic
2025-07-09 add bridge rectifier to PoE
2025-07-11 replace lan transformer with a 2 channel version
2025-07-11 work on temperature sensor
2025-07-11 replace USB micro with USB c
2025-07-14 add connection to FAN PWM and TACH
2025-07-14 start with layout of ethernet and PoE
2025-07-14 place components of PoE
2025-07-14 place USB footprints
2025-07-15 place temperature sensor footprint
2025-07-15 finish placement
2025-07-15 improve placement of temperature sensor
2025-07-15 define layers for routing
2025-07-15 start with routing
2025-07-15 prepare generation of fabrication files
2025-07-15 route temperature sensor
2025-07-15 update symbols from library
2025-07-15 add missing routes
2025-07-15 fix DRC errors
2025-07-15 fix silkscreen
2025-07-15 create fabrication files for temperature sensor R01
